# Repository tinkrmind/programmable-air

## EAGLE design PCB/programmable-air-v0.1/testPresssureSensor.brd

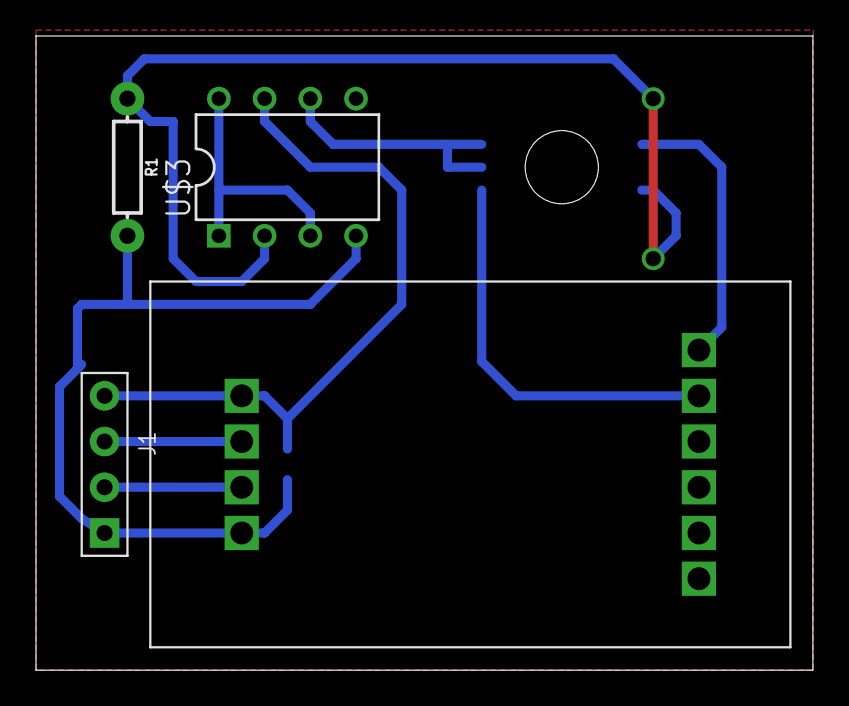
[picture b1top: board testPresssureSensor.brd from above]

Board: 2 copper layers, 43.2 x 35.2 mm, 6 parts (1 on the bottom side), 9 nets.

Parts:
C1: 0.1uF; 0603
J1: 4p-2.54; H4-2.54
R1: 1k; AXIAL-0.3
U$1: 2SMPP-03
U$2: HX711
U$3: LM10CN; DIP8

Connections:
GND: C1.2, J1.1, R1.P$2, U$2.P$7, U$3.4
unnamed: U$1.P$4, U$2.P$5
unnamed: U$3.1, U$3.3, U$3.8
unnamed: U$1.P$5, U$1.P$6, U$3.6
unnamed: R1.P$1, U$1.P$3, U$3.2
unnamed: U$1.P$1, U$2.P$6
unnamed: J1.2, U$2.P$8
unnamed: J1.3, U$2.P$9
VIN: C1.1, J1.4, U$2.P$10, U$3.7

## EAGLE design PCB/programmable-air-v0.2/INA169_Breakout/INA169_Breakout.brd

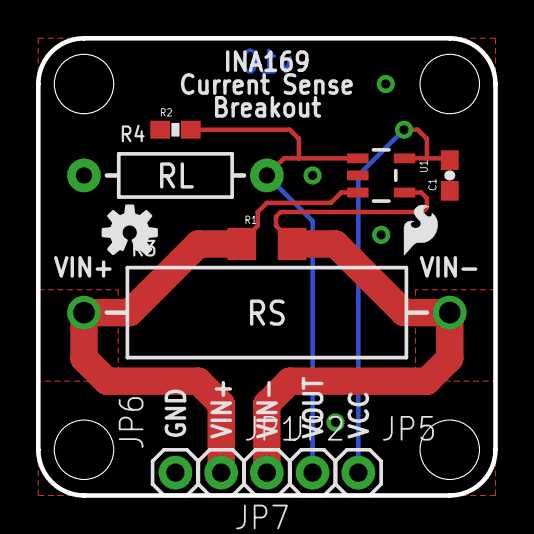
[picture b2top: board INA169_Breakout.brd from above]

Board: 2 copper layers, 25.4 x 25.4 mm, 19 parts (1 on the bottom side), 5 nets.

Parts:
C1: 0.1uF; 0603-CAP
FRAME1: FRAME-LETTER; CREATIVE_COMMONS
JP1, JP2, JP5, JP6, JP7: M01PTH; 1X01
LOGO1: SFE_LOGO_NAME_FLAME.1_INCH; SFE_LOGO_NAME_FLAME_.1
LOGO2: OSHW-LOGOS; OSHW-LOGO-S
LOGO3: LOGO-SFESK; SFE-LOGO-FLAME
R1: 10; 1206
R2: 10k; 0603-RES
R3: AXIAL-0.8
R4: AXIAL-0.4
STANDOFF1, STANDOFF2, STANDOFF3, STANDOFF4: STAND-OFF
U1: INA169; SOT23-5

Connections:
GND: C1.1, JP6.1, R2.1, R4.P$1, U1.2
VCC: C1.2, JP5.1, U1.5
VIN+: JP1.1, R1.1, R3.P$1, U1.3
VIN-: JP2.1, R1.2, R3.P$2, U1.4
VOUT: JP7.1, R2.2, R4.P$2, U1.1

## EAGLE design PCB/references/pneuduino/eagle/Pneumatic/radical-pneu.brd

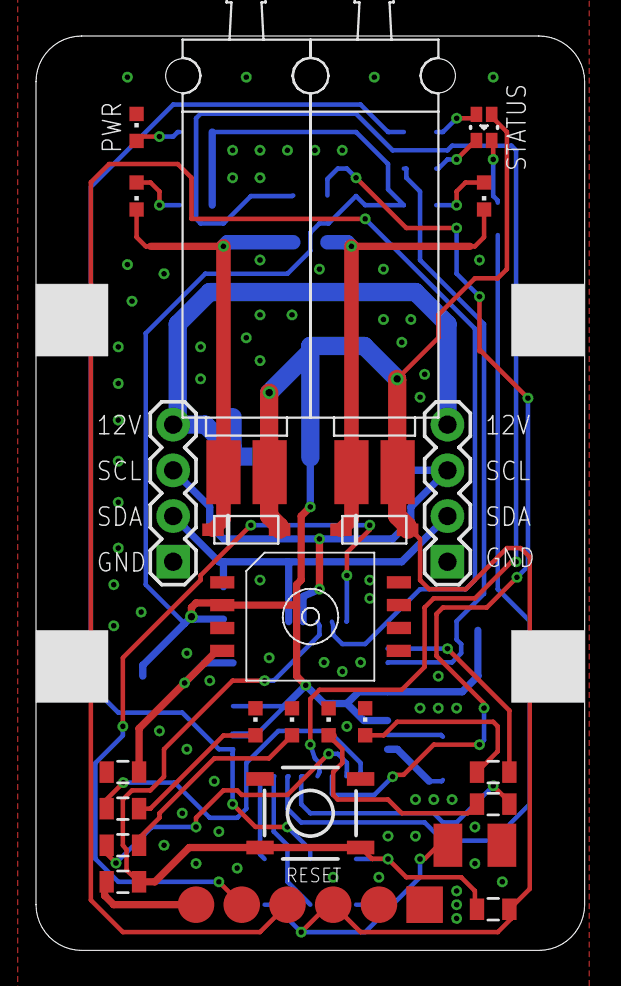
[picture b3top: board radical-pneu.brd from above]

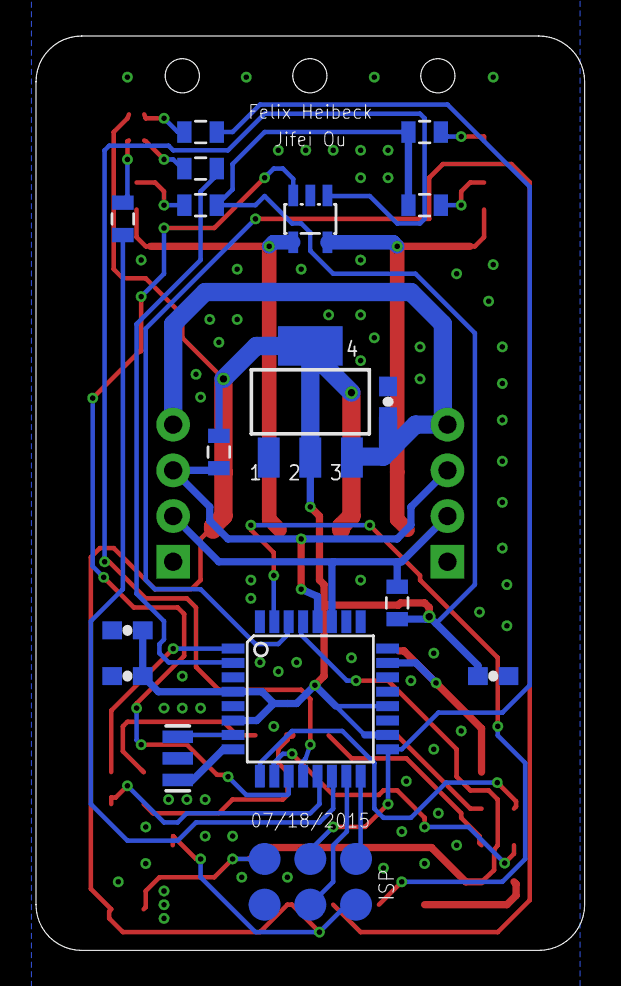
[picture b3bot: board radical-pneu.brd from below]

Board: 2 copper layers, 30.5 x 50.8 mm, 41 parts (17 on the bottom side), 35 nets.

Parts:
1, 2, 3, 5, 7, 8: CHIPLED_0603
C1, C2, C8, C10: 0.1uF; 0603-CAP
C3: 22uF; SMC_B
C5: 0.1uF; 0805
C7: 470pF; 0805
D1, D2: SOD-123
IC3: ATMEGA328; TQFP32-08
JP2, JP3: 1X04
PWR: CHIPLED_0603
Q1: 16Mhz; RESONATOR-SMD
R1, R2, R4, R7, R8, R9, R10, R11, R12, R13: 1k; 0805
R3: 10K; 0805
R5, R6: 4.7k; 0805
S1: TAC_SWITCHSMD; TACTILE-SWITCH-SMD
U2: NCP1117-5; LINEAR_SOT223
U$1: MPXHZ6400
U$3: QS5K2; SOT23-5L
U$10: ISP_POGO; POGO_ISP
U$11: S070V-2VALVE; S070C-2
U$12: FTDI_POGO
U$21: LTST-C19FD1WT; LTST

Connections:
+5V: C2.1, C3.+, C8.1, C10.1, D1.C, D2.C, IC3.4, IC3.6, IC3.18, IC3.20, R2.2, R3.1, R5.1, R6.2, R8.2, R11.2, U2.2, U2.4, U$1.2, U$10.2, U$11.1-2, U$11.2-2, U$12.4, U$21.+
A0/PRESSURE: C7.2, IC3.23, U$1.4
D3: IC3.1, R1.2
D4: IC3.2, R9.2
D5: IC3.9, R7.2
D6: IC3.10, R4.2
D7: IC3.11, U$3.3
D8: IC3.12, U$3.1
D9: IC3.13, R10.2
D10: IC3.14, R12.2
DTR: C5.2, U$12.1
GND: 1.C, 5.C, 7.C, 8.C, C1.2, C2.2, C3.-, C7.1, C8.2, C10.2, IC3.3, IC3.5, IC3.21, JP2.1, JP3.1, PWR.C, Q1.2, S1.1, S1.2, U2.1, U$1.3, U$3.2, U$10.6, U$12.5, U$12.6
M1_VGND: 2.C, D1.A, U$3.4, U$11.2-1
M2_VGND: 3.C, D2.A, U$3.5, U$11.1-1
MISO: IC3.16, U$10.1
MOSI: IC3.15, U$10.4
unnamed: 8.A, R4.1
unnamed: 7.A, R7.1
unnamed: IC3.8, Q1.1
unnamed: 1.A, R1.1
unnamed: 2.A, R2.1
unnamed: 3.A, R8.1
unnamed: IC3.7, Q1.3
unnamed: 5.A, R10.1
unnamed: PWR.A, R11.1
unnamed: R9.1, U$21.R
unnamed: R12.1, U$21.G
unnamed: R13.1, U$21.B
RESET: C5.1, IC3.29, R3.2, S1.3, S1.4, U$10.5
RX: IC3.30, U$12.3
SCK: IC3.17, R13.2, U$10.3
SCL: IC3.28, JP2.3, JP3.3, R6.1
SDA: IC3.27, JP2.2, JP3.2, R5.2
TX: IC3.31, U$12.2
VIN: C1.1, JP2.4, JP3.4, U2.3

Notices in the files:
parts and their libraries:
SparkFun-Capacitors: Licensing: Creative Commons ShareAlike 4.0 International - https://creativecommons.org/licenses/by-sa/4.0
SparkFun-Aesthetics: Licensing: CC v3.0 Share-Alike You are welcome to use this library for commercial purposes.
